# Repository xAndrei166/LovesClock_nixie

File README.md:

# Lovesclock
first time making this shit

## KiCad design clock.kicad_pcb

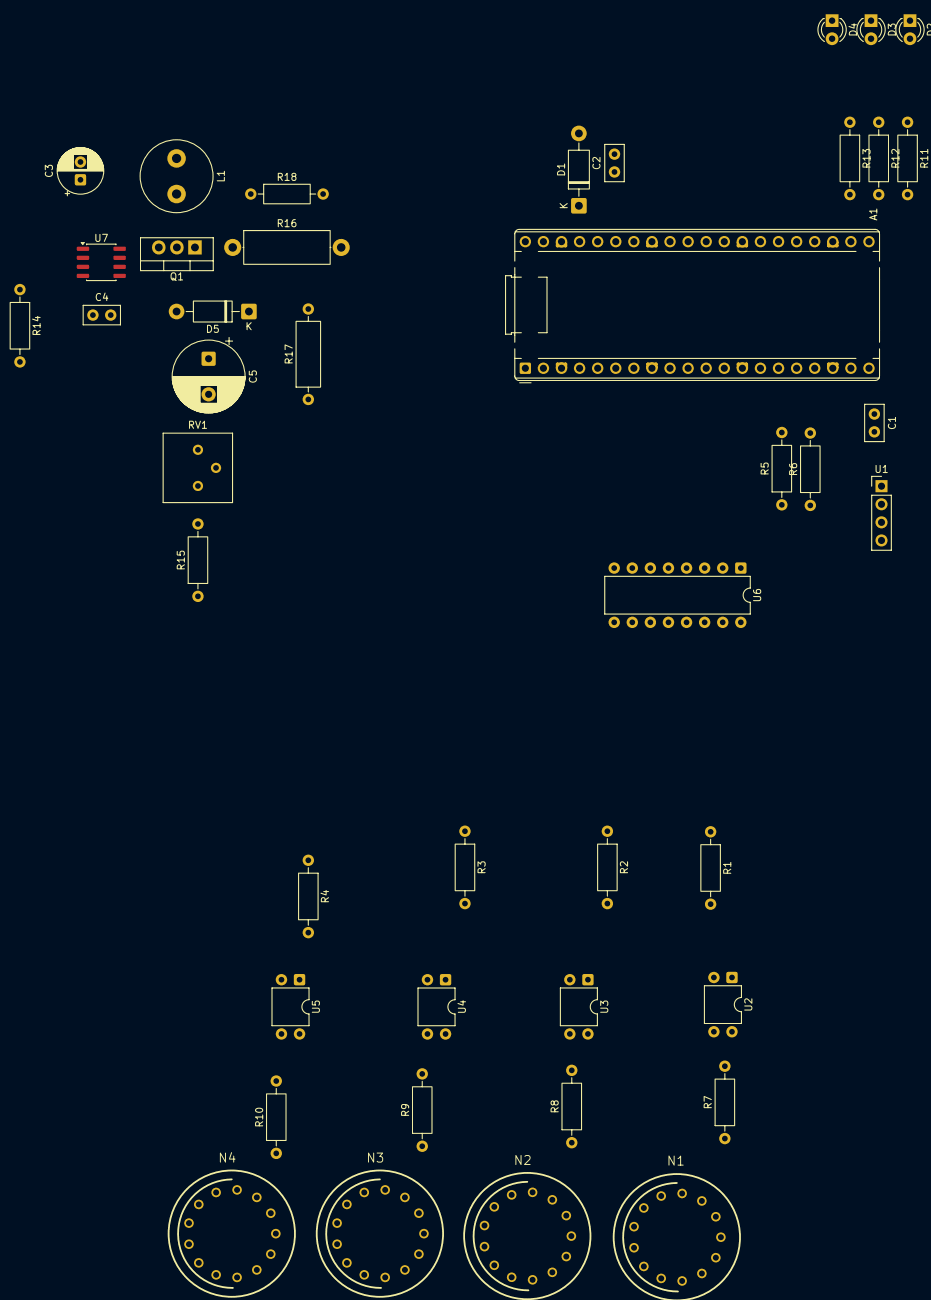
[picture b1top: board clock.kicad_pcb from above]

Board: 2 copper layers, 43 parts (0 on the bottom side), 49 nets, no tracks yet.

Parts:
A1: RaspberryPi_Pico_W; RaspberryPi_Pico_Common_THT
C1, C2, C4: 100nF; C_Disc_D5.0mm_W2.5mm_P2.50mm
C3: 47uF >16V; CP_Radial_D6.3mm_P2.50mm
C5: 2.2µF - 4.7µF; CP_Radial_D10.0mm_P5.00mm
D1: D_Schottky; D_DO-41_SOD81_P10.16mm_Horizontal
D2, D3, D4: LED; LED_D3.0mm
D5: UF4004; D_DO-41_SOD81_P10.16mm_Horizontal
L1: 100µH; L_Radial_D10.0mm_P5.00mm_Fastron_07M
N1, N2, N3, N4: IN-14; nixies-us-IN-14
Q1: AOTF10N60; TO-220-3_Vertical
R1, R2, R3, R4: 470; R_Axial_DIN0207_L6.3mm_D2.5mm_P10.16mm_Horizontal
R5, R6: 4.7K; R_Axial_DIN0207_L6.3mm_D2.5mm_P10.16mm_Horizontal
R7, R8, R9, R10: 10K; R_Axial_DIN0207_L6.3mm_D2.5mm_P10.16mm_Horizontal
R11, R12, R13: 330; R_Axial_DIN0207_L6.3mm_D2.5mm_P10.16mm_Horizontal
R14: 1M; R_Axial_DIN0207_L6.3mm_D2.5mm_P10.16mm_Horizontal
R15: 7.5k; R_Axial_DIN0207_L6.3mm_D2.5mm_P10.16mm_Horizontal
R16: 0.1; R_Axial_DIN0414_L11.9mm_D4.5mm_P15.24mm_Horizontal
R17: 470K; R_Axial_DIN0309_L9.0mm_D3.2mm_P12.70mm_Horizontal
R18: 10k; R_Axial_DIN0207_L6.3mm_D2.5mm_P10.16mm_Horizontal
RV1: 5k Trim; Potentiometer_Bourns_3386P_Vertical
U1: DS3231M; PinHeader_1x04_P2.54mm_Vertical
U2, U3, U4, U5: TLP627; DIP-4_W7.62mm
U6: K155NA1; DIP-16_W7.62mm
U7: MAX1771xSA; SO-8_3.9x4.9mm_P1.27mm

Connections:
+5V: C2.2, C3.2, D1.2 (A), L1.1, U6.5 (VCC), U7.2 (V+)
/+170v: C5.1, D5.1 (K), R14.2, R17.2, U2.4, U3.4, U4.4, U5.4
/DIGIT_1: N1.A, R7.1
/DIGIT_2: N2.A, R8.1
/DIGIT_3: N3.A, R9.1
/DIGIT_4: N4.A, R10.1
/K155_A: A1.11 (GPIO8), U6.3 (A)
/K155_B: A1.12 (GPIO9), U6.6 (B)
/K155_C: A1.14 (GPIO10), U6.7 (C)
/K155_D: A1.15 (GPIO11), U6.4 (D)
/TUBE_1: A1.9 (GPIO6), R1.1
/TUBE_2: A1.7 (GPIO5), R2.1
/TUBE_3: A1.6 (GPIO4), R3.1
/TUBE_4: A1.5 (GPIO3), R4.1
/rtc_3v3: A1.36 (3V3), C1.1, R5.1, R6.1, U1.2 (VCC)
GND: A1.3 (GND), A1.8 (GND), A1.13 (GND), A1.18 (GND), A1.23 (GND), A1.28 (GND), A1.38 (GND), C1.2, C2.1, C3.1, C4.1, C5.2, D2.1 (K), D3.1 (K), D4.1 (K), R16.2, R17.1, R18.2, RV1.2, RV1.3, U2.2, U3.2, U4.2, U5.2, U6.12 (GND), U7.4 (SHDN), U7.6 (AGND), U7.7 (GND)
unnamed: A1.10 (GPIO7), U1.3 (~INT/SQW)
unnamed: A1.16 (I2C0_SDA), R6.2
unnamed: A1.17 (I2C0_SCL), R5.2
unnamed: A1.21 (GPIO16), R11.2
unnamed: A1.22 (GPIO17), R12.2
unnamed: A1.24 (GPIO18), R13.1
unnamed: A1.39 (VSYS), D1.1 (K)
unnamed: D2.2 (A), R11.1
unnamed: D3.2 (A), R12.1
unnamed: D4.2 (A), R13.2
unnamed: D5.2 (A), L1.2, Q1.2 (D)
unnamed: Q1.1 (G), Q1.3 (S), R16.1, R18.1, U7.1 (EXT), U7.8 (CS)
unnamed: R1.2, U2.1
unnamed: R2.2, U3.1
unnamed: R3.2, U4.1
unnamed: R4.2, U5.1
unnamed: R7.2, U2.3
unnamed: R8.2, U3.3
unnamed: R9.2, U4.3
unnamed: R10.2, U5.3
unnamed: R15.2, RV1.1
unnamed: N1.0, N2.0, N3.0, N4.0, U6.16 (0)
unnamed: N1.1, N2.1, N3.1, N4.1, U6.15 (1)
unnamed: N1.2, N2.2, N3.2, N4.2, U6.8 (2)
unnamed: N1.3, N2.3, N3.3, N4.3, U6.9 (3)
unnamed: N1.4, N2.4, N3.4, N4.4, U6.13 (4)
unnamed: N1.5, N2.5, N3.5, N4.5, U6.14 (5)
unnamed: N1.6, N2.6, N3.6, N4.6, U6.11 (6)
unnamed: N1.7, N2.7, N3.7, N4.7, U6.10 (7)
unnamed: N1.8, N2.8, N3.8, N4.8, U6.1 (8)
unnamed: N1.9, N2.9, N3.9, N4.9, U6.2 (9)
unnamed: R14.1, R15.1, U7.3 (FB)
unnamed: C4.2, U7.5 (REF)
